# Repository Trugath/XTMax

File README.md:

# XTMax

XTMax is an 8-bit ISA expansion card built around a Teensy 4.1. This repository contains the Teensy firmware, the BIOS extension ROM and DOS-side storage/memory drivers, floppy image tooling, and KiCad hardware files.

This repository is a forked extraction of the XTMax fragment originally published in the MicroCoreLabs Projects monorepo at [`XTMax/Code/XTMax`](https://github.com/MicroCoreLabs/Projects/tree/master/XTMax/Code/XTMax).

This fork is a personal project aimed at using XTMax with my IBM 5155 (Portable PC); bring-up notes, timing defaults, and harness targets often reflect that machine, even though much of the stack applies to other PC/XT-class systems too.

Unless a subdirectory or file says otherwise, this fork is distributed under the MIT license in [LICENSE](./LICENSE), which lists copyright holders (including upstream authors) and paths that use other licenses. Some bundled components keep their own original licensing, for example [software/sd/LICENSE.TXT](./software/sd/LICENSE.TXT).

## Repository Layout

- [`firmware/teensy`](./firmware/teensy): Teensy 4.1 firmware, generated Boot ROM header, and machine-specific notes.
- [`software`](./software): Boot ROM source, DOS storage/EMS/UMB drivers, prebuilt binaries, and legacy build toolchains.
- [`images`](./images): prebuilt MS-DOS driver disk images and notes.
- [`hardware`](./hardware): KiCad source files, schematic PDF, and generated fabrication outputs.
- [`host`](./host): host-side tools, including the Rust USB-link utility for XTMax remote-control work.
- [`scripts`](./scripts): host-side tooling, currently for building the floppy images.
- [`tests`](./tests): host-side verification for repo-maintained behaviors that can be checked without hardware.
- [`docs/REPO_LAYOUT.md`](./docs/REPO_LAYOUT.md): quick map of which files are primary sources, generated artifacts, and helper assets.

## Start Here

If you are trying to:

- Flash firmware: read [`firmware/teensy/AGENTS.md`](./firmware/teensy/AGENTS.md).
- Understand ISA decode, option ROM placement, or IBM 5155 coexistence: read [`firmware/teensy/IO_PORTS.md`](./firmware/teensy/IO_PORTS.md).
- Use or rebuild the DOS drivers: read [`software/README.md`](./software/README.md).
- Work on the host-side USB link or remote-console tooling: start with [`host/xtmax-host`](./host/xtmax-host).
- Refresh the floppy images: read [`images/README.txt`](./images/README.txt) and run [`scripts/build_xtmax_floppy.py`](./scripts/build_xtmax_floppy.py).
- Work on the Boot ROM SD stack: start with [`software/bootrom/bootrom.asm`](./software/bootrom/bootrom.asm), then regenerate [`firmware/teensy/bootrom.h`](./firmware/teensy/bootrom.h).

## Build And Update Paths

### Teensy firmware

The primary firmware source is [`firmware/teensy/teensy.ino`](./firmware/teensy/teensy.ino).

- Arduino IDE + Teensyduino: open `firmware/teensy/teensy.ino`, select `Teensy 4.1`, and upload.
- Optional CLI: `arduino-cli compile --fqbn teensy:avr:teensy41 firmware/teensy`

### Boot ROM

The Boot ROM source lives in [`software/bootrom/bootrom.asm`](./software/bootrom/bootrom.asm). The firmware consumes the generated header at [`firmware/teensy/bootrom.h`](./firmware/teensy/bootrom.h).

Typical refresh flow from [`software/bootrom`](./software/bootrom):

```bash
nasm -f bin -o bootrom bootrom.asm
python3 checksum.py
python3 generate_header.py
```

### Floppy images

From the repo root:

```bash
pip install -r scripts/requirements-floppy.txt
python3 scripts/build_xtmax_floppy.py
```

This refreshes the driver/data disk images in [`images`](./images).

## Current Constraints

- Hardware validation is still required for firmware, ROM timing, and ISA-bus behavior.
- The repo contains both source files and checked-in generated artifacts such as ROM headers, binaries, floppy images, and PCB fabrication files.
- DOS driver sources are preserved alongside prebuilt binaries for convenience.

## Notes For Maintainers

- If you change SD register behavior or the Boot ROM protocol, update both firmware and ROM artifacts together.
- If you change `MMAN_BASE`, `SD_BASE`, or the ROM mapping assumptions, re-check [`firmware/teensy/IO_PORTS.md`](./firmware/teensy/IO_PORTS.md) and [`software/README.md`](./software/README.md).
- Keep generated cache files out of the repo; root ignore rules cover common Python/macOS noise, but tracked historical artifacts remain as-is.

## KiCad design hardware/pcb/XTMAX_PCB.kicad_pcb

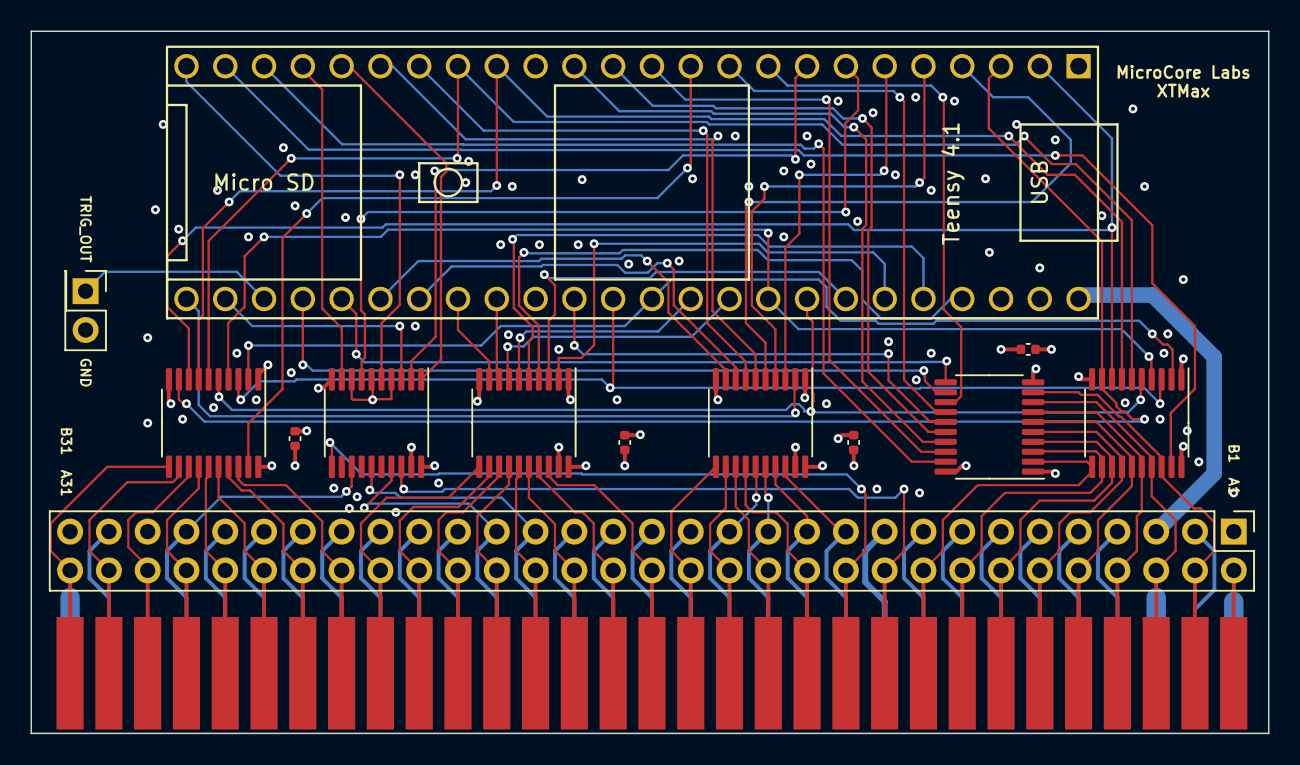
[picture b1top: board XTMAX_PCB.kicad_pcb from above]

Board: 4 copper layers, 81.0 x 46.0 mm, 14 parts (0 on the bottom side), 102 nets.

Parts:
C1, C2, C3, C4: 10 uF; C_0402_1005Metric
J1: Bus_ISA_8bit; isa
J2: Conn_02x31_Odd_Even; PinHeader_2x31_P2.54mm_Vertical
J3: Conn_02x01; PinHeader_2x01_P2.54mm_Vertical
U1, U3, U4, U7, U8: SN74LVC245A; TSSOP-20_4.4x6.5mm_P0.65mm
U2: Teensy4.1; Teensy41_Ted_Modified
U5: SN74LVC244; TSSOP-20_4.4x6.5mm_P0.65mm

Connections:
+3V3: C1.1, C2.1, C3.1, C4.1, U1.20 (VCC), U2.46 (3V3), U3.20 (VCC), U4.20 (VCC), U5.20 (VCC), U7.20 (VCC), U8.20 (VCC)
+5V: J1.B03 (VCC), J2.5, U2.48 (VIN)
A01: J1.A01 (IO), J2.2
B02: J1.B02 (RESET), J2.3
B04: J1.B04 (IRQ2), J2.7
B05: J1.B05 (-5V), J2.9
B06: J1.B06 (DRQ2), J2.11
B07: J1.B07 (-12V), J2.13
B08: J1.B08 (UNUSED), J2.15
B09: J1.B09 (+12V), J2.17
B15: J1.B15 (~DACK3), J2.29
B16: J1.B16 (DRQ3), J2.31
B17: J1.B17 (~DACK1), J2.33
B18: J1.B18 (DRQ1), J2.35
B21: J1.B21 (IRQ7), J2.41
B22: J1.B22 (IRQ6), J2.43
B23: J1.B23 (IRQ5), J2.45
B24: J1.B24 (IRQ4), J2.47
B25: J1.B25 (IRQ3), J2.49
B26: J1.B26 (~DACK2), J2.51
B27: J1.B27 (TC), J2.53
B30: J1.B30 (OSC), J2.59
DATA_OE_n: U2.22 (30_CRX3), U3.19 (CE)
GND: C1.2, C2.2, C3.2, C4.2, J1.B01 (GND), J1.B10 (GND), J1.B31 (GND), J2.1, J2.19, J2.61, J3.2, U1.1 (A->B), U1.10 (GND), U2.1 (GND), U2.34 (GND), U2.47 (GND), U3.1 (A->B), U3.10 (GND), U4.1 (A->B), U4.10 (GND), U4.19 (CE), U5.4 (I1a), U5.6 (I2a), U5.8 (I3a), U5.10 (GND), U5.19 (OEb), U7.1 (A->B), U7.10 (GND), U8.1 (A->B), U8.10 (GND), U8.19 (CE)
ISA_A0: J1.A31 (A00), J2.62, U7.11 (B7)
ISA_A1: J1.A30 (BA01), J2.60, U7.12 (B6)
ISA_A2: J1.A29 (BA02), J2.58, U7.13 (B5)
ISA_A3: J1.A28 (BA03), J2.56, U7.14 (B4)
ISA_A4: J1.A27 (BA04), J2.54, U7.15 (B3)
ISA_A5: J1.A26 (BA05), J2.52, U7.16 (B2)
ISA_A6: J1.A25 (BA06), J2.50, U7.17 (B1)
ISA_A7: J1.A24 (BA07), J2.48, U7.18 (B0)
ISA_A8: J1.A23 (BA08), J2.46, U8.11 (B7)
ISA_A9: J1.A22 (BA09), J2.44, U8.12 (B6)
ISA_A10: J1.A21 (BA10), J2.42, U8.13 (B5)
ISA_A11: J1.A20 (BA11), J2.40, U8.14 (B4)
ISA_A12: J1.A19 (BA12), J2.38, U8.15 (B3)
ISA_A13: J1.A18 (BA13), J2.36, U8.16 (B2)
ISA_A14: J1.A17 (BA14), J2.34, U8.17 (B1)
ISA_A15: J1.A16 (BA15), J2.32, U8.18 (B0)
ISA_A16: J1.A15 (BA16), J2.30, U4.11 (B7)
ISA_A17: J1.A14 (BA17), J2.28, U4.12 (B6)
ISA_A18: J1.A13 (BA18), J2.26, U4.13 (B5)
ISA_A19: J1.A12 (BA19), J2.24, U4.14 (B4)
ISA_AEN: J1.A11 (AEN), J2.22, U5.11 (I0b)
ISA_BALE: J1.B28 (ALE), J2.55, U5.13 (I1b)
ISA_CHRDY: J1.A10 (IO_READY), J2.20, U5.18 (O0a)
ISA_CLK: J1.B20 (CLK), J2.39, U5.17 (I3b)
ISA_D0: J1.A09 (DB0), J2.18, U1.11 (B7), U3.2 (A0)
ISA_D1: J1.A08 (DB1), J2.16, U1.12 (B6), U3.3 (A1)
ISA_D2: J1.A07 (DB2), J2.14, U1.13 (B5), U3.4 (A2)
ISA_D3: J1.A06 (DB3), J2.12, U1.14 (B4), U3.5 (A3)
ISA_D4: J1.A05 (DB4), J2.10, U1.15 (B3), U3.6 (A4)
ISA_D5: J1.A04 (DB5), J2.8, U1.16 (B2), U3.7 (A5)
ISA_D6: J1.A03 (DB6), J2.6, U1.17 (B1), U3.8 (A6)
ISA_D7: J1.A02 (DB7), J2.4, U1.18 (B0), U3.9 (A7)
ISA_IOR: J1.B14 (~IOR), J2.27, U4.15 (B3)
ISA_IOW: J1.B13 (~IOW), J2.25, U4.16 (B2)
ISA_MEMR: J1.B12 (~SMEMR), J2.23, U4.17 (B1)
ISA_MEMW: J1.B11 (~SMEMW), J2.21, U4.18 (B0)
ISA_REFRESH: J1.B19 (~DACK0), J2.37, U5.15 (I2b)
MUX_ADDR_n: U2.11 (9_OUT1C), U7.19 (CE)
MUX_DATA_n: U1.19 (CE), U2.23 (31_CTX3)
TEENSY_CHRDY: U2.8 (6_OUT1D), U5.2 (I0a)
Teensy_A0: U1.9 (A7), U2.3 (1_TX1_CTX2_MISO1), U7.9 (A7)
Teensy_A1: U1.8 (A6), U2.2 (0_RX1_CRX2_CS1), U7.8 (A6)
Teensy_A2: U1.7 (A5), U2.16 (24_A10_TX6_SCL2), U7.7 (A5)
Teensy_A3: U1.6 (A4), U2.17 (25_A11_RX6_SDA2), U7.6 (A4)
Teensy_A4: U1.5 (A3), U2.41 (19_A5_SCL), U7.5 (A3)
Teensy_A5: U1.4 (A2), U2.40 (18_A4_SDA), U7.4 (A2)
Teensy_A6: U1.3 (A1), U2.36 (14_A0_TX3_SPDIF_OUT), U7.3 (A1)
Teensy_A7: U1.2 (A0), U2.37 (15_A1_RX3_SPDIF_IN), U7.2 (A0)
Teensy_A8: U2.32 (40_A16), U8.9 (A7)
Teensy_A9: U2.33 (41_A17), U8.8 (A6)
Teensy_A10: U2.39 (17_A3_TX4_SDA1), U8.7 (A5)
Teensy_A11: U2.38 (16_A2_RX4_SCL1), U8.6 (A4)
Teensy_A12: U2.44 (22_A8_CTX1), U8.5 (A3)
Teensy_A13: U2.45 (23_A9_CRX1_MCLK1), U8.4 (A2)
Teensy_A14: U2.42 (20_A6_TX5_LRCLK1), U8.3 (A1)
Teensy_A15: U2.43 (21_A7_RX5_BCLK1), U8.2 (A0)
Teensy_A16: U2.30 (38_CS1_IN1), U4.9 (A7)
Teensy_A17: U2.31 (39_MISO1_OUT1A), U4.8 (A6)
Teensy_A18: U2.18 (26_A12_MOSI1), U4.7 (A5)
Teensy_A19: U2.19 (27_A13_SCK1), U4.6 (A4)
Teensy_AEN: U2.21 (29_TX7), U5.9 (O0b)
Teensy_BALE: U2.7 (5_IN2), U5.7 (O1b)
Teensy_CHRDY: U2.20 (28_RX7), U5.1 (OEa)
Teensy_CLK: U2.26 (34_RX8), U5.3 (O3b)
Teensy_IOR: U2.4 (2_OUT2), U4.5 (A3)
Teensy_IOW: U2.5 (3_LRCLK2), U4.4 (A2)
Teensy_MEMR: U2.6 (4_BCLK2), U4.3 (A1)
Teensy_MEMW: U2.25 (33_MCLK2), U4.2 (A0)
Teensy_OUT_D0: U2.12 (10_CS_MQSR), U3.18 (B0)
Teensy_OUT_D1: U2.14 (12_MISO_MQSL), U3.17 (B1)
Teensy_OUT_D2: U2.13 (11_MOSI_CTX1), U3.16 (B2)
Teensy_OUT_D3: U2.35 (13_SCK_LED), U3.15 (B3)
Teensy_OUT_D4: U2.10 (8_TX2_IN1), U3.14 (B4)
Teensy_OUT_D5: U2.9 (7_RX2_OUT1A), U3.13 (B5)
Teensy_OUT_D6: U2.28 (36_CS), U3.12 (B6)
Teensy_OUT_D7: U2.29 (37_CS), U3.11 (B7)
Teensy_REFRESH: U2.24 (32_OUT1B), U5.5 (O2b)
Teensy_TRIG_OUT: J3.1, U2.27 (35_TX8)

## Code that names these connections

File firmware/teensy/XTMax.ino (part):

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#define PIN_IOWR_n          3
#define PIN_IORD_n          2
   
#define PIN_MUX_DATA_n      31     
#define PIN_DATA_OE_n       30     
#define PIN_MUX_ADDR_n      9
#define PIN_TRIG_OUT        35
 
#define PIN_ADDR19          27
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  pinMode(PIN_IOWR_n,         INPUT);
  pinMode(PIN_IORD_n,         INPUT);
 
  pinMode(PIN_MUX_DATA_n,     OUTPUT);   
  pinMode(PIN_DATA_OE_n,      OUTPUT);   
  pinMode(PIN_MUX_ADDR_n,     OUTPUT);
  pinMode(PIN_TRIG_OUT,       OUTPUT);
 
  pinMode(PIN_ADDR19,         INPUT);
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  digitalWriteFast(PIN_CHRDY_OE_n,   0x1);
  digitalWriteFast(PIN_CHRDY_OUT,    0x0);
 
  digitalWriteFast(PIN_DATA_OE_n,    0x1);
  digitalWriteFast(PIN_MUX_ADDR_n,   0x0);
  digitalWriteFast(PIN_MUX_DATA_n,   0x1);
  digitalWriteFast(PIN_TRIG_OUT,     0x1);
 

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
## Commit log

2026-04-01 Update SD card handling and docs
2026-04-01 Reorganize repo layout
2026-04-01 Refactor Teensy shared core
2026-04-01 Add MAME test harness
2026-04-02 Add ibm5160 MAME driver flow
2026-04-02 Add MAME assertion script
2026-04-02 Add XTMax MAME phase 1
2026-04-02 Add XTMax MAME SD model
2026-04-02 Improve XTMax MAME boot test
2026-04-02 Add XTMax Boot ROM regressions
2026-04-02 Add XTMax storage regression
2026-04-02 Add XTMax EMS regression
2026-04-02 Restore Boot ROM text output
2026-04-02 Add license and provenance note
2026-04-02 Add Boot ROM service menu
2026-04-02 Add Boot ROM service loader
2026-04-03 Add XTMax service menu
2026-04-03 Improve Boot ROM prompt
2026-04-03 Add XTMax host link foundation
2026-04-03 Add XTMax host utility
2026-04-03 Add XTMax text mirror
2026-04-03 Add MAME mirror regression
2026-04-03 Improve AGENTS guides
2026-04-03 Fix MAME menu test keyboard timing on POST
    Made-with: Cursor
2026-04-03 Add run_all_tests script
    Made-with: Cursor
2026-04-03 Add GETTING_STARTED guide
    Made-with: Cursor
2026-04-03 Add XTMax USB ROM dump FIFO
    Made-with: Cursor
2026-04-03 Add MAME ROM capture via Teensy USB
    Made-with: Cursor
2026-04-03 Note personal IBM 5155 focus in README
    Made-with: Cursor
2026-04-03 Update LICENSE copyright and third-party notice
    Made-with: Cursor

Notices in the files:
firmware/teensy/XTMax.ino:
Copyright (c) 2024 Ted Fried
